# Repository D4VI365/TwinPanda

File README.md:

# TwinPanda
 Custom Split Wireless Keyboard (nRF52840)
 Un progetto di tastiera meccanica split custom, progettata per essere compatta, ergonomica e completamente wireless grazie alla tecnologia Bluetooth.
 Caratteristiche Principali
 Cervello: Basata su Seeed Studio XIAO nRF52840, ideale per un basso consumo energetico e connettività Bluetooth integrata.
 Espansione I/O: Utilizzo di un chip MCP23017 (SSOP-28) per gestire la matrice dei tasti tramite protocollo $I^2C$.
 Layout Ergonomico: Layout split da 76 tasti ottimizzato per il comfort.
 Case Custom: Progettato in Fusion 360 per essere stampato in 3D con un top frame da 4.5 mm e inserti filettati M3 per la massima solidità.
 Gestione Batteria: Circuito di Battery Sense integrato per il monitoraggio in tempo reale della carica tramite partitore di tensione ($820k\Ohm / 2M\Ohm$).
 
Case:

Full assembly:

PCB Design:

Left Schematic:

Right Schematic:

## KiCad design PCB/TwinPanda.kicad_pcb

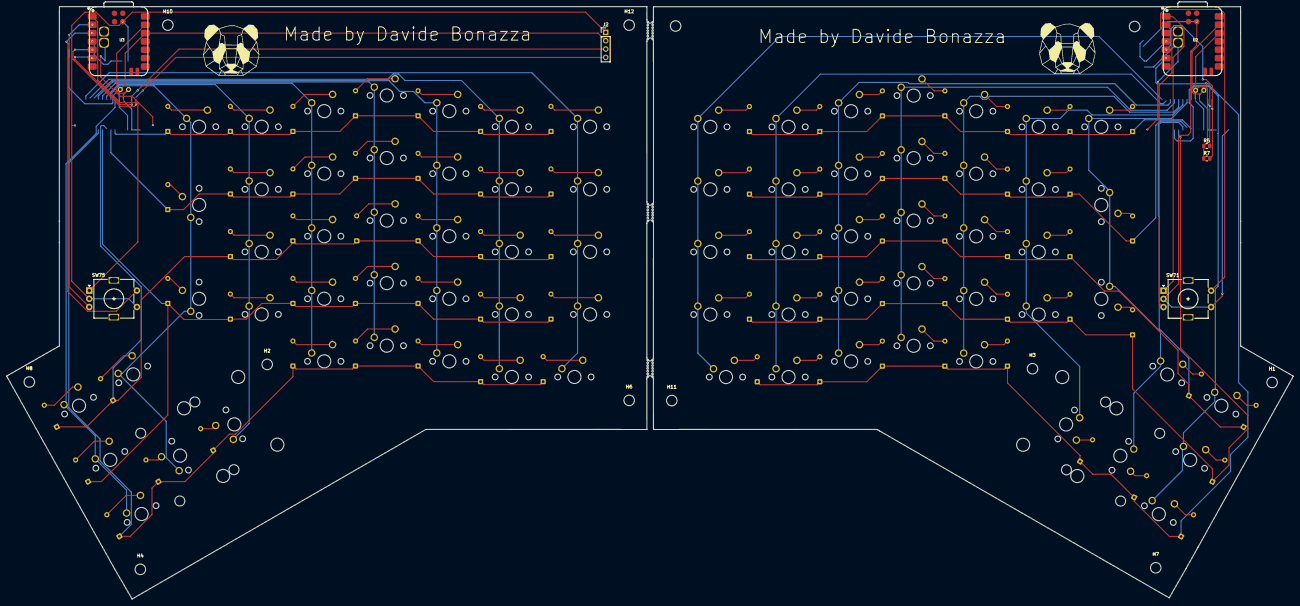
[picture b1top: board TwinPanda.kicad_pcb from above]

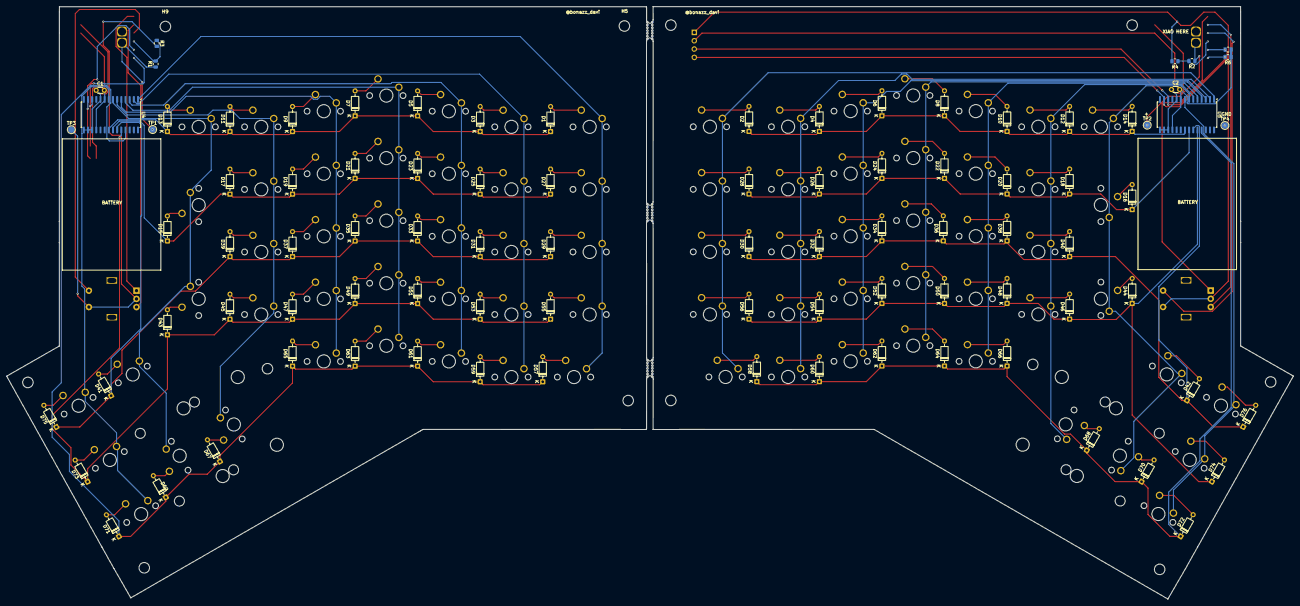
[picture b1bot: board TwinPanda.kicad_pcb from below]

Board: 2 copper layers, 391.8 x 180.3 mm, 188 parts (90 on the bottom side), 122 nets.

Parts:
BO0, BO1, BO2: MouseBites; MouseBite-Slot_2.0x4.5mm_outset_D0.5mm_P0.85mm_7h
C1, C2: C_Small; C_Disc_D3.0mm_W1.6mm_P2.50mm
D1, D2: 0-0; D_DO-35_SOD27_P7.62mm_Horizontal
D3, D4: 0-1; D_DO-35_SOD27_P7.62mm_Horizontal
D5, D6: 0-2; D_DO-35_SOD27_P7.62mm_Horizontal
D7, D8: 0-3; D_DO-35_SOD27_P7.62mm_Horizontal
D9, D10: 0-4; D_DO-35_SOD27_P7.62mm_Horizontal
D11, D12: 0-5; D_DO-35_SOD27_P7.62mm_Horizontal
D13, D14: 0-6; D_DO-35_SOD27_P7.62mm_Horizontal
D15, D16: 1-6; D_DO-35_SOD27_P7.62mm_Horizontal
D17, D18: 1-5; D_DO-35_SOD27_P7.62mm_Horizontal
D19, D20: 1-4; D_DO-35_SOD27_P7.62mm_Horizontal
D21, D22: 1-3; D_DO-35_SOD27_P7.62mm_Horizontal
D23, D24: 1-2; D_DO-35_SOD27_P7.62mm_Horizontal
D25, D26: 1-1; D_DO-35_SOD27_P7.62mm_Horizontal
D27, D28: 1-0; D_DO-35_SOD27_P7.62mm_Horizontal
D29, D30: 2-0; D_DO-35_SOD27_P7.62mm_Horizontal
D31, D32: 2-1; D_DO-35_SOD27_P7.62mm_Horizontal
D33, D34: 2-2; D_DO-35_SOD27_P7.62mm_Horizontal
D35, D36: 2-3; D_DO-35_SOD27_P7.62mm_Horizontal
D37, D38: 2-4; D_DO-35_SOD27_P7.62mm_Horizontal
D39, D40: 2-5; D_DO-35_SOD27_P7.62mm_Horizontal
D41, D42: t0-1; D_DO-35_SOD27_P7.62mm_Horizontal
D43, D44: 3-6; D_DO-35_SOD27_P7.62mm_Horizontal
D45, D46: 3-5; D_DO-35_SOD27_P7.62mm_Horizontal
D47, D48: 3-4; D_DO-35_SOD27_P7.62mm_Horizontal
D49, D50: 3-3; D_DO-35_SOD27_P7.62mm_Horizontal
D51, D52: 3-2; D_DO-35_SOD27_P7.62mm_Horizontal
D53, D54: 3-1; D_DO-35_SOD27_P7.62mm_Horizontal
D55, D56: 3-0; D_DO-35_SOD27_P7.62mm_Horizontal
D57, D58: 4-0; D_DO-35_SOD27_P7.62mm_Horizontal
D59, D60: 4-1; D_DO-35_SOD27_P7.62mm_Horizontal
D61, D62: 4-2; D_DO-35_SOD27_P7.62mm_Horizontal
D63, D64: 4-3; D_DO-35_SOD27_P7.62mm_Horizontal
D65, D66: 4-4; D_DO-35_SOD27_P7.62mm_Horizontal
D67, D68: t2-0; D_DO-35_SOD27_P7.62mm_Horizontal
D69, D70: t2-1; D_DO-35_SOD27_P7.62mm_Horizontal
D71, D72: t2-2; D_DO-35_SOD27_P7.62mm_Horizontal
D73, D74: t1-2; D_DO-35_SOD27_P7.62mm_Horizontal
D75, D76: t0-2; D_DO-35_SOD27_P7.62mm_Horizontal
H1, H2, H3, H4, H5, H6, H7, H8, H9, H10, H11, H12: MountingHole; MountingHole_3.2mm_M3
J2: Conn_01x04_Socket; PinHeader_1x04_P2.54mm_Vertical
R1, R2: 806K; R_0805_2012Metric
R3, R4: 2M; R_0805_2012Metric
R5, R6, R7, R8: 4.7k; R_0805_2012Metric
SW1, SW2: 4-0; SW_MX_1u
SW3, SW4: 4-1; SW_MX_1u
SW5, SW6: 4-2; SW_MX_1u
SW7, SW8: 4-3; SW_MX_1u
SW9, SW10: 4-4; SW_MX_1u
SW11: t2-0; SW_MX_1u
SW12: T2-0; SW_MX_1u
SW13: t2-1; SW_MX_1u
SW14: T2-1; SW_MX_1u
SW15, SW22: 3-0; SW_MX_1.5u
SW16, SW23: 3-1; SW_MX_1u
SW17, SW24: 3-2; SW_MX_1u
SW18, SW25: 3-3; SW_MX_1u
SW19, SW26: 3-4; SW_MX_1u
SW20, SW27: 3-5; SW_MX_1u
SW21, SW28: 3-6; SW_MX_1.5u
SW29, SW36: 2-0; SW_MX_1.5u
SW30, SW37: 2-1; SW_MX_1u
SW31, SW38: 2-2; SW_MX_1u
SW32, SW39: 2-3; SW_MX_1u
SW33, SW40: 2-4; SW_MX_1u
SW34, SW41: 2-5; SW_MX_1u
SW35: t0-1; SW_MX_1u
SW42: T0-1; SW_MX_1u
SW43, SW50: 1-0; SW_MX_1.5u
SW44, SW51: 1-1; SW_MX_1u
SW45, SW52: 1-2; SW_MX_1u
SW46, SW53: 1-3; SW_MX_1u
SW47, SW54: 1-4; SW_MX_1u
SW48, SW55: 1-5; SW_MX_1u
SW49, SW56: 1-6; SW_MX_1.5u
SW57, SW64: 0-0; SW_MX_1.5u
SW58, SW65: 0-1; SW_MX_1u
SW59, SW66: 0-2; SW_MX_1u
SW60, SW67: 0-3; SW_MX_1u
SW61, SW68: 0-4; SW_MX_1u
SW62, SW69: 0-5; SW_MX_1u
SW63, SW70: 0-6; SW_MX_1u
SW71, SW75: RotaryEncoder_Switch; RotaryEncoder_Alps_EC11E-Switch_Vertical_H20mm
SW72: t0-2; SW_MX_1u
SW73: t1-2; SW_MX_1u
SW74: t2-2; SW_MX_1u
SW77: T0-2; SW_MX_1u
SW78: T1-2; SW_MX_1u
SW79: T2-2; SW_MX_1u
TP1, TP2, TP3, TP4: TestPoint; TestPoint_Pad_D2.0mm
U2, U3: XIAO-nRF52840-SMD; modified-XIAO-nRF52840-SMD
U4, U5: MCP23017_SO; SOIC-28W_7.5x17.9mm_P1.27mm

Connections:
/Left/3V3: C1.2, R5.1, R7.1, U2.12 (3V3), U4.9 (VDD), U4.18 (~RESET)
/Left/BT_PIN: R1.2, R3.1, U2.4 (P0.29_A3_D3)
/Left/COL0: SW1.1, SW15.1, SW29.1, SW43.1, SW57.1, U4.1 (GPB0)
/Left/COL1: SW3.1, SW16.1, SW30.1, SW44.1, SW58.1, U4.2 (GPB1)
/Left/COL2: SW5.1, SW17.1, SW31.1, SW45.1, SW59.1, U4.3 (GPB2)
/Left/COL3: SW7.1, SW18.1, SW32.1, SW46.1, SW60.1, U4.4 (GPB3)
/Left/COL4: SW9.1, SW19.1, SW33.1, SW47.1, SW61.1, U4.5 (GPB4)
/Left/COL5: SW11.1, SW20.1, SW34.1, SW48.1, SW62.1, U4.6 (GPB5)
/Left/COL6: SW13.1, SW21.1, SW35.1, SW49.1, SW63.1, U4.7 (GPB6)
/Left/COL7: SW72.1, SW73.1, SW74.1, U4.8 (GPB7)
/Left/D0: SW71.A, U2.1 (P0.02_A0_D0)
/Left/D1: SW71.B, U2.2 (P0.03_A1_D1)
/Left/D2: SW71.S2, U2.3 (P0.28_A2_D2)
/Left/GND: R3.2, SW71.C, SW71.S1, TP3.1, U2.22 (GND)
/Left/ROW0: D1.1 (K), D3.1 (K), D5.1 (K), D7.1 (K), D9.1 (K), D11.1 (K), D13.1 (K), U4.21 (GPA0)
/Left/ROW1: D15.1 (K), D17.1 (K), D19.1 (K), D21.1 (K), D23.1 (K), D25.1 (K), D27.1 (K), U4.22 (GPA1)
/Left/ROW2: D29.1 (K), D31.1 (K), D33.1 (K), D35.1 (K), D37.1 (K), D39.1 (K), D41.1 (K), D75.1 (K), U4.23 (GPA2)
/Left/ROW3: D43.1 (K), D45.1 (K), D47.1 (K), D49.1 (K), D51.1 (K), D53.1 (K), D55.1 (K), D73.1 (K), U4.24 (GPA3)
/Left/ROW4: D57.1 (K), D59.1 (K), D61.1 (K), D63.1 (K), D65.1 (K), D67.1 (K), D69.1 (K), D71.1 (K), U4.25 (GPA4)
/Left/SCL: R5.2, U2.6 (P0.05_A5_D5_SCL), U4.12 (SCK)
/Left/SDA: R7.2, U2.5 (P0.04_A4_D4_SDA), U4.13 (SDA)
/Left/VBAT: R1.1, TP1.1, U2.15 (BAT)
/Right/3V3: C2.2, J2.2, R6.1, R8.1, U3.12 (3V3), U5.9 (VDD), U5.18 (~RESET)
/Right/BT_PIN: R2.2, R4.1, U3.4 (P0.29_A3_D3)
/Right/COL0: SW2.1, SW22.1, SW36.1, SW50.1, SW64.1, U5.1 (GPB0)
/Right/COL1: SW4.1, SW23.1, SW37.1, SW51.1, SW65.1, U5.2 (GPB1)
/Right/COL2: SW6.1, SW24.1, SW38.1, SW52.1, SW66.1, U5.3 (GPB2)
/Right/COL3: SW8.1, SW25.1, SW39.1, SW53.1, SW67.1, U5.4 (GPB3)
/Right/COL4: SW10.1, SW26.1, SW40.1, SW54.1, SW68.1, U5.5 (GPB4)
/Right/COL5: SW12.1, SW27.1, SW41.1, SW55.1, SW69.1, U5.6 (GPB5)
/Right/COL6: SW14.1, SW28.1, SW42.1, SW56.1, SW70.1, U5.7 (GPB6)
/Right/COL7: SW77.1, SW78.1, SW79.1, U5.8 (GPB7)
/Right/D0: SW75.A, U3.1 (P0.02_A0_D0)
/Right/D1: SW75.B, U3.2 (P0.03_A1_D1)
/Right/D2: SW75.S2, U3.3 (P0.28_A2_D2)
/Right/GND: J2.1, R4.2, SW75.C, SW75.S1, TP4.1, U3.22 (GND)
/Right/ROW0: D2.1 (K), D4.1 (K), D6.1 (K), D8.1 (K), D10.1 (K), D12.1 (K), D14.1 (K), U5.21 (GPA0)
/Right/ROW1: D16.1 (K), D18.1 (K), D20.1 (K), D22.1 (K), D24.1 (K), D26.1 (K), D28.1 (K), U5.22 (GPA1)
/Right/ROW2: D30.1 (K), D32.1 (K), D34.1 (K), D36.1 (K), D38.1 (K), D40.1 (K), D42.1 (K), D76.1 (K), U5.23 (GPA2)
/Right/ROW3: D44.1 (K), D46.1 (K), D48.1 (K), D50.1 (K), D52.1 (K), D54.1 (K), D56.1 (K), D74.1 (K), U5.24 (GPA3)
/Right/ROW4: D58.1 (K), D60.1 (K), D62.1 (K), D64.1 (K), D66.1 (K), D68.1 (K), D70.1 (K), D72.1 (K), U5.25 (GPA4)
/Right/SCL: J2.3, R6.2, U3.6 (P0.05_A5_D5_SCL), U5.12 (SCK)
/Right/SDA: J2.4, R8.2, U3.5 (P0.04_A4_D4_SDA), U5.13 (SDA)
/Right/VBAT: R2.1, TP2.1, U3.15 (BAT)
unnamed: D1.2 (A), SW57.2
unnamed: D2.2 (A), SW64.2
unnamed: D3.2 (A), SW58.2
unnamed: D4.2 (A), SW65.2
unnamed: D5.2 (A), SW59.2
unnamed: D6.2 (A), SW66.2
unnamed: D7.2 (A), SW60.2
unnamed: D8.2 (A), SW67.2
unnamed: D9.2 (A), SW61.2
unnamed: D10.2 (A), SW68.2
unnamed: D11.2 (A), SW62.2
unnamed: D12.2 (A), SW69.2
unnamed: D13.2 (A), SW63.2
unnamed: D14.2 (A), SW70.2
unnamed: D15.2 (A), SW49.2
unnamed: D16.2 (A), SW56.2
unnamed: D17.2 (A), SW48.2
unnamed: D18.2 (A), SW55.2
unnamed: D19.2 (A), SW47.2
unnamed: D20.2 (A), SW54.2
unnamed: D21.2 (A), SW46.2
unnamed: D22.2 (A), SW53.2
unnamed: D23.2 (A), SW45.2
unnamed: D24.2 (A), SW52.2
unnamed: D25.2 (A), SW44.2
unnamed: D26.2 (A), SW51.2
unnamed: D27.2 (A), SW43.2
unnamed: D28.2 (A), SW50.2
unnamed: D29.2 (A), SW29.2
unnamed: D30.2 (A), SW36.2
unnamed: D31.2 (A), SW30.2
unnamed: D32.2 (A), SW37.2
unnamed: D33.2 (A), SW31.2
unnamed: D34.2 (A), SW38.2
unnamed: D35.2 (A), SW32.2
unnamed: D36.2 (A), SW39.2
unnamed: D37.2 (A), SW33.2
unnamed: D38.2 (A), SW40.2
unnamed: D39.2 (A), SW34.2
unnamed: D40.2 (A), SW41.2
unnamed: D41.2 (A), SW35.2
unnamed: D42.2 (A), SW42.2
unnamed: D43.2 (A), SW21.2
unnamed: D44.2 (A), SW28.2
unnamed: D45.2 (A), SW20.2
unnamed: D46.2 (A), SW27.2
unnamed: D47.2 (A), SW19.2
unnamed: D48.2 (A), SW26.2
unnamed: D49.2 (A), SW18.2
unnamed: D50.2 (A), SW25.2
unnamed: D51.2 (A), SW17.2
unnamed: D52.2 (A), SW24.2
unnamed: D53.2 (A), SW16.2
unnamed: D54.2 (A), SW23.2
unnamed: D55.2 (A), SW15.2
unnamed: D56.2 (A), SW22.2
unnamed: D57.2 (A), SW1.2
unnamed: D58.2 (A), SW2.2
unnamed: D59.2 (A), SW3.2
unnamed: D60.2 (A), SW4.2
unnamed: D61.2 (A), SW5.2
unnamed: D62.2 (A), SW6.2
unnamed: D63.2 (A), SW7.2
unnamed: D64.2 (A), SW8.2
unnamed: D65.2 (A), SW9.2
unnamed: D66.2 (A), SW10.2
unnamed: D67.2 (A), SW11.2
unnamed: D68.2 (A), SW12.2
unnamed: D69.2 (A), SW13.2
unnamed: D70.2 (A), SW14.2
unnamed: D71.2 (A), SW74.2
unnamed: D72.2 (A), SW79.2
unnamed: D73.2 (A), SW73.2
unnamed: D74.2 (A), SW78.2
unnamed: D75.2 (A), SW72.2
unnamed: D76.2 (A), SW77.2
unnamed: C1.1, U2.13 (GND), U4.10 (VSS), U4.15 (A0), U4.16 (A1), U4.17 (A2)
unnamed: C2.1, U3.13 (GND), U5.10 (VSS), U5.15 (A0), U5.16 (A1), U5.17 (A2)

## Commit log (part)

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2025-12-26 Added the files
2025-12-26 Updated files
2026-01-20 Add assembly and PCB schematic images
    Added FullAssembly.png to Images and LSchematic.png, RSchematic.png, and PCB.png to PCB directory for documentation and reference purposes.
2026-01-23 Update BOM, PCB layout, and assembly images
    Updated BOM.csv with new suppliers, lower prices, and alternative links for several components. Modified the PCB layout (TwinPanda.kicad_pcb) with significant changes to component and mounting hole p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
2026-01-31 Update BOM with new prices, suppliers, and links
    Updated the Bill of Materials to reflect new prices, suppliers, and product links for multiple components. Some quantities and sources have changed, and total price has been recalculated. Added empty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
2026-01-31 Update BOM component prices
    Adjusted prices for several components in BOM.csv, including Switches, Diodes, Rotary Encoder, OLED screen, key stabilizer, M3 Heat-press insert, and M3 Screws. Updated the total price to reflect the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
2026-02-02 Update BOM currency label to USD
    Changed the 'Total price' column header in BOM.csv from an invalid character to 'Total price USD' for clarity.
2026-02-02 Simplify and update BOM component links
    Shortened and standardized URLs for several components in BOM.csv to remove tracking parameters and improve readability. Also updated the total price row and made minor formatting adjustments.
2026-02-02 Remove BOM.csv and move build.yaml to Firmware/
    Deleted the BOM.csv file and relocated build.yaml to the Firmware directory. This cleans up the project structure and organizes build configuration files.
2026-02-16 Add TwinPanda.f3z CAD model
    Add a new Fusion 360 archive (TwinPanda.f3z) to the CAD directory. This commits the initial binary CAD design source for the TwinPanda project.
2026-05-07 update
    bugfix
